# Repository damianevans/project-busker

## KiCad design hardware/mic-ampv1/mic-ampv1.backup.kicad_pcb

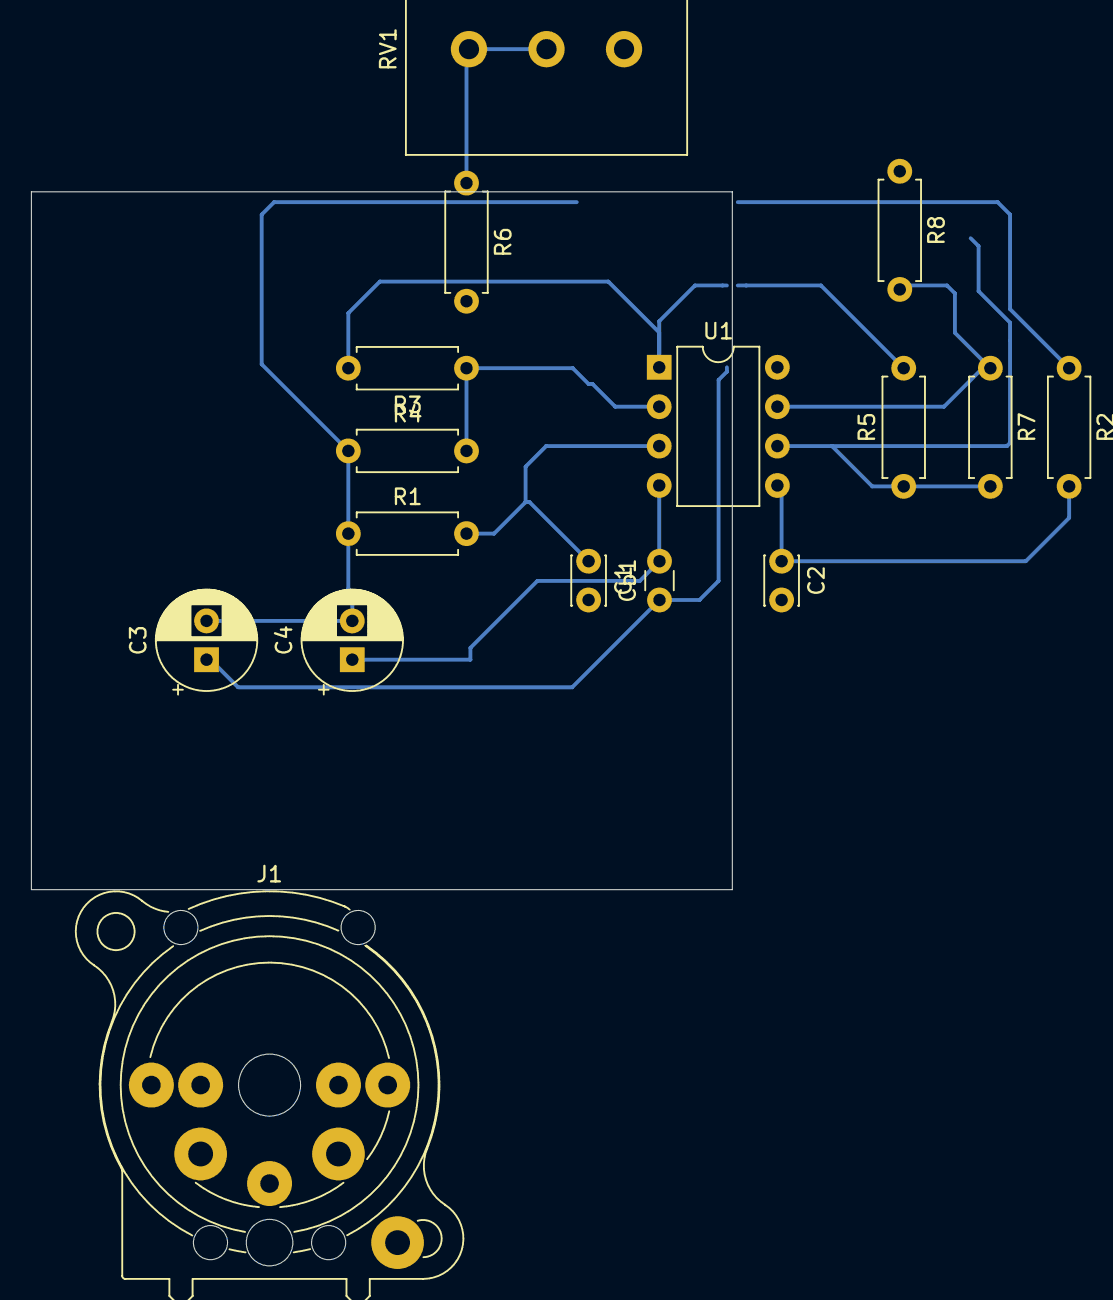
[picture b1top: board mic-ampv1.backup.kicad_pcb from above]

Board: 2 copper layers, 45.2 x 45.0 mm, 16 parts (0 on the bottom side), 12 nets.

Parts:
C1, C2: 150nF; C_Disc_D3.0mm_W2.0mm_P2.50mm
C3, C4: 10uF; CP_Radial_D6.3mm_P2.50mm
Cb1: 100nF; C_Disc_D3.0mm_W1.6mm_P2.50mm
J1: XLR3_Switched; Jack_XLR-6.35mm_Neutrik_NCJ6FA-V-0_Vertical
R1, R2, R3, R4, R5, R7: 10K; R_Axial_DIN0207_L6.3mm_D2.5mm_P7.62mm_Horizontal
R6: 270; R_Axial_DIN0207_L6.3mm_D2.5mm_P7.62mm_Horizontal
R8: 100; R_Axial_DIN0207_L6.3mm_D2.5mm_P7.62mm_Horizontal
RV1: 10K; Potentiometer_Alps_RK163_Single_Horizontal
U1: NE5532; DIP-8_W7.62mm

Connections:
+12V: C3.1, Cb1.1, U1.8
-12V: C4.1, Cb1.2, U1.4
GND: C3.2, C4.2, R1.1, R2.1, R4.1
unnamed: C1.1, R1.2, U1.3
unnamed: C1.2, J1.3
unnamed: C2.1, R2.2, U1.5
unnamed: C2.2, J1.2
unnamed: R3.1, R4.2, R6.2, U1.2
unnamed: R3.2, R5.2, U1.1
unnamed: R5.1, R7.2, RV1.1, U1.6
unnamed: R6.1, RV1.2, RV1.3
unnamed: R7.1, R8.2, U1.7
